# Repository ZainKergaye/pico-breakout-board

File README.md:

# Pico Breakout Board

This is a project that debugs my z-board. The purpose of this is to copy the exact placement of the
RP2040 chip and it's accessories and then allow further breakout

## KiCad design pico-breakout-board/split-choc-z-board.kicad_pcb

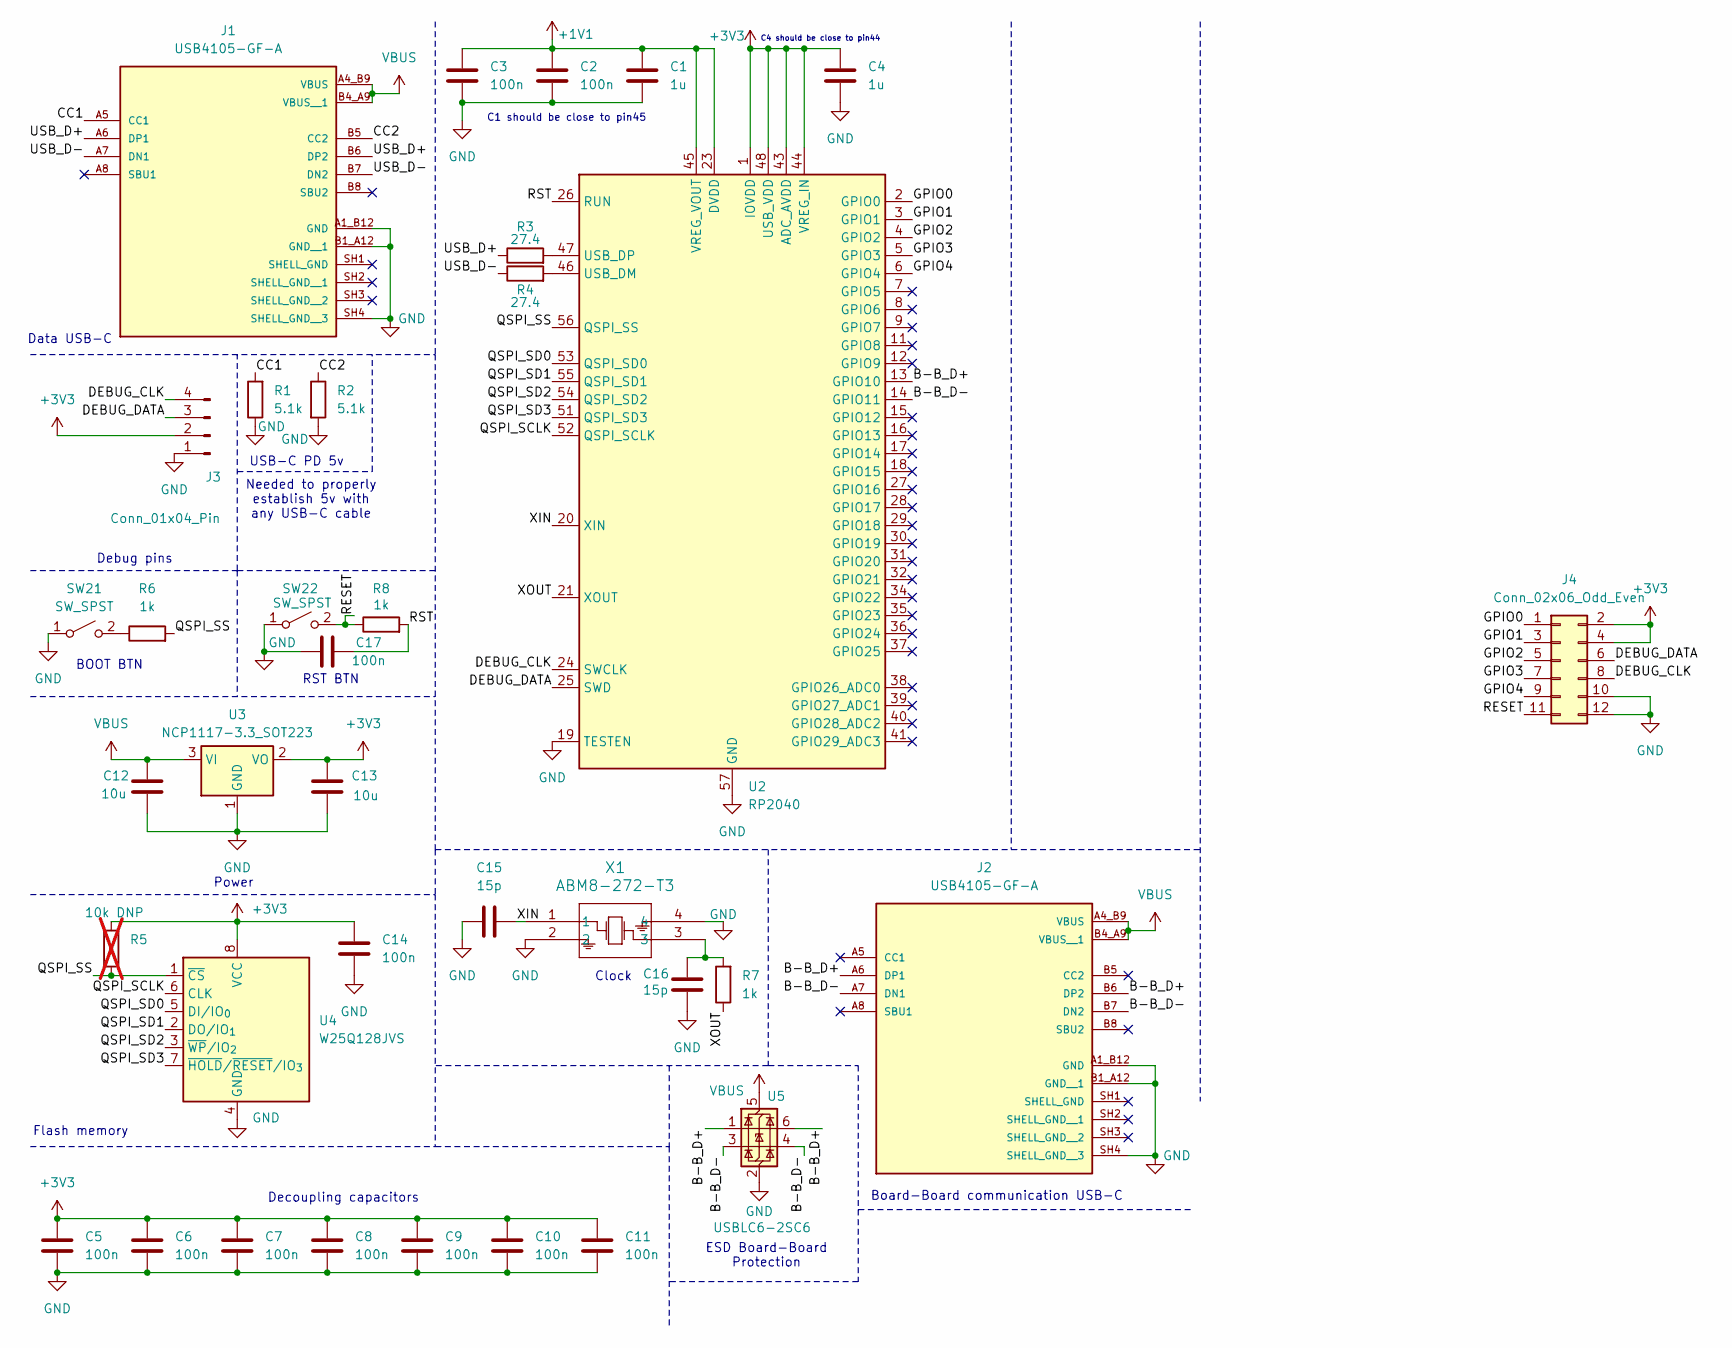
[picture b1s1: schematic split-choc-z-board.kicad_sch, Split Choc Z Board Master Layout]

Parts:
C1, C4: 1u; C_0402_1005Metric
C2, C3, C5, C6, C7, C8, C9, C10, C11, C14, C17: 100n; C_0402_1005Metric
C12, C13: 10u; C_0402_1005Metric
C15, C16: 15p; C_0402_1005Metric
J1, J2: USB4105-GF-A; GCT_USB4105-GF-A; PARTREV B4
J3: Conn_01x04_Pin; PinHeader_1x04_P2.54mm_Vertical
J4: Conn_02x06_Odd_Even; PinSocket_2x06_P2.54mm_Vertical
R1, R2: 5.1k; R_0603_1608Metric
R3, R4: 27.4; R_0603_1608Metric
R5: 10k DNP; R_0603_1608Metric; not fitted
R6, R7, R8: 1k; R_0603_1608Metric
SW21, SW22: SW_SPST; SW_TL3315NF250Q
U2: RP2040; QFN-56-1EP_7x7mm_P0.4mm_EP3.2x3.2mm
U3: NCP1117-3.3_SOT223; SOT-223-3_TabPin2
U4: W25Q128JVS; SOIC-8_5.3x5.3mm_P1.27mm
U5: USBLC6-2SC6; SOT-23-6
X1: ABM8-272-T3; ABM8-272-T3_ABR

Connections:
+1V1: C1.1, C2.1, C3.1, U2.23 (DVDD), U2.45 (VREG_VOUT), U2.50 (DVDD)
+3V3: C4.1, C5.1, C6.1, C7.1, C8.1, C9.1, C10.1, C11.1, C13.1, C14.1, J3.2, J4.2, J4.4, R5.1, U2.1 (IOVDD), U2.10 (IOVDD), U2.22 (IOVDD), U2.33 (IOVDD), U2.42 (IOVDD), U2.43 (ADC_AVDD), U2.44 (VREG_IN), U2.48 (USB_VDD), U2.49 (IOVDD), U3.2 (VO), U4.8 (VCC)
/B-B_D+: J2.A6 (DP1), J2.B6 (DP2), U2.13 (GPIO10), U5.1 (I/O1), U5.6 (I/O1)
/B-B_D-: J2.A7 (DN1), J2.B7 (DN2), U2.14 (GPIO11), U5.3 (I/O2), U5.4 (I/O2)
/CC1: J1.A5 (CC1), R1.2
/CC2: J1.B5 (CC2), R2.1
/DEBUG_CLK: J3.4, J4.8, U2.24 (SWCLK)
/DEBUG_DATA: J3.3, J4.6, U2.25 (SWD)
/GPIO0: J4.1, U2.2 (GPIO0)
/GPIO1: J4.3, U2.3 (GPIO1)
/GPIO2: J4.5, U2.4 (GPIO2)
/GPIO3: J4.7, U2.5 (GPIO3)
/GPIO4: J4.9, U2.6 (GPIO4)
/QSPI_SCLK: U2.52 (QSPI_SCLK), U4.6 (CLK)
/QSPI_SD0: U2.53 (QSPI_SD0), U4.5 (DI/IO_{0})
/QSPI_SD1: U2.55 (QSPI_SD1), U4.2 (DO/IO_{1})
/QSPI_SD2: U2.54 (QSPI_SD2), U4.3 (~WP/IO_{2})
/QSPI_SD3: U2.51 (QSPI_SD3), U4.7 (~HOLD/~RESET/IO_{3})
/QSPI_SS: R5.2, R6.2, U2.56 (QSPI_SS), U4.1 (~CS)
/RESET: J4.11, R8.1, SW22.2 (B)
/RST: C17.2, R8.2, U2.26 (RUN)
/USB_D+: J1.A6 (DP1), J1.B6 (DP2), R3.1
/USB_D-: J1.A7 (DN1), J1.B7 (DN2), R4.1
/XIN: C15.2, U2.20 (XIN), X1.1
/XOUT: R7.1, U2.21 (XOUT)
GND: C1.2, C2.2, C3.2, C4.2, C5.2, C6.2, C7.2, C8.2, C9.2, C10.2, C11.2, C12.2, C13.2, C14.2, C15.1, C16.2, C17.1, J1.A1_B12 (GND), J1.B1_A12 (GND__1), J1.SH4 (SHELL_GND__3), J2.A1_B12 (GND), J2.B1_A12 (GND__1), J2.SH4 (SHELL_GND__3), J3.1, J4.10, J4.12, R1.1, R2.2, SW21.1 (A), SW22.1 (A), U2.19 (TESTEN), U2.57 (GND), U3.1 (GND), U4.4 (GND), U5.2 (GND), X1.2, X1.4
unnamed: C16.1, R7.2, X1.3
unnamed: R6.1, SW21.2 (B)
unnamed: R4.2, U2.46 (USB_DM)
unnamed: R3.2, U2.47 (USB_DP)
VBUS: C12.1, J1.A4_B9 (VBUS), J1.B4_A9 (VBUS__1), J2.A4_B9 (VBUS), J2.B4_A9 (VBUS__1), U3.3 (VI), U5.5 (VBUS)

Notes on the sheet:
BOOT BTN
Clock
RST BTN
Flash memory
C1 should be close to pin45
Data USB-C
Board-Board communication USB-C
Debug pins
C4 should be close to pin44
USB-C PD 5v
Decoupling capacitors
Power
ESD Board-Board Protection
Needed to properly establish 5v with any USB-C cable

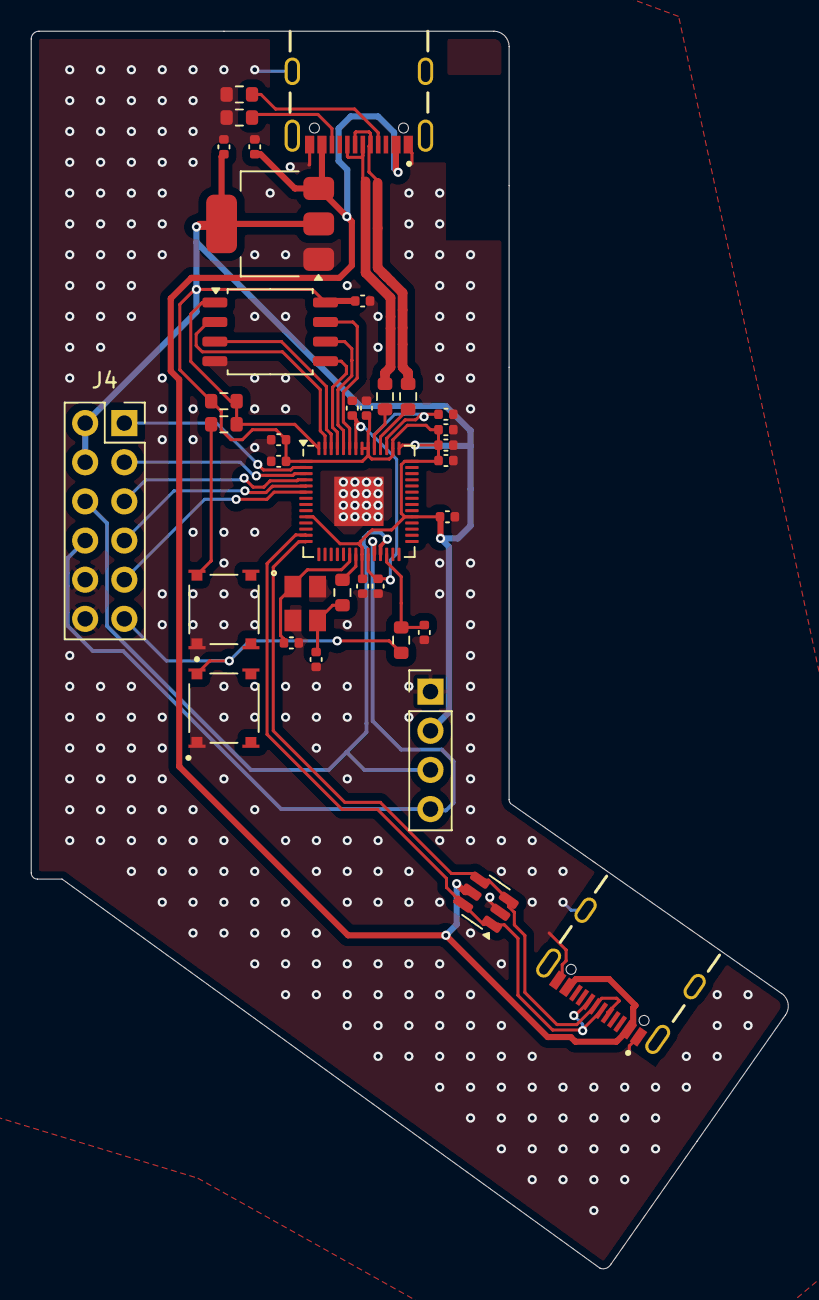
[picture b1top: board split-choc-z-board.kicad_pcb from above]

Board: 2 copper layers, 49.1 x 80.3 mm, 36 parts (0 on the bottom side), 31 nets.

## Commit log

2025-09-25 Removed matrix and added 2.54mm pins 2x20
2025-09-29 Finished bare redesign
2025-09-29 Forgot no connects
2025-09-29 Generated gerbers :)
2025-10-04 Completed first design review redesign
2025-10-04 Added gerbers
2025-10-06 Completed second design review redesign
